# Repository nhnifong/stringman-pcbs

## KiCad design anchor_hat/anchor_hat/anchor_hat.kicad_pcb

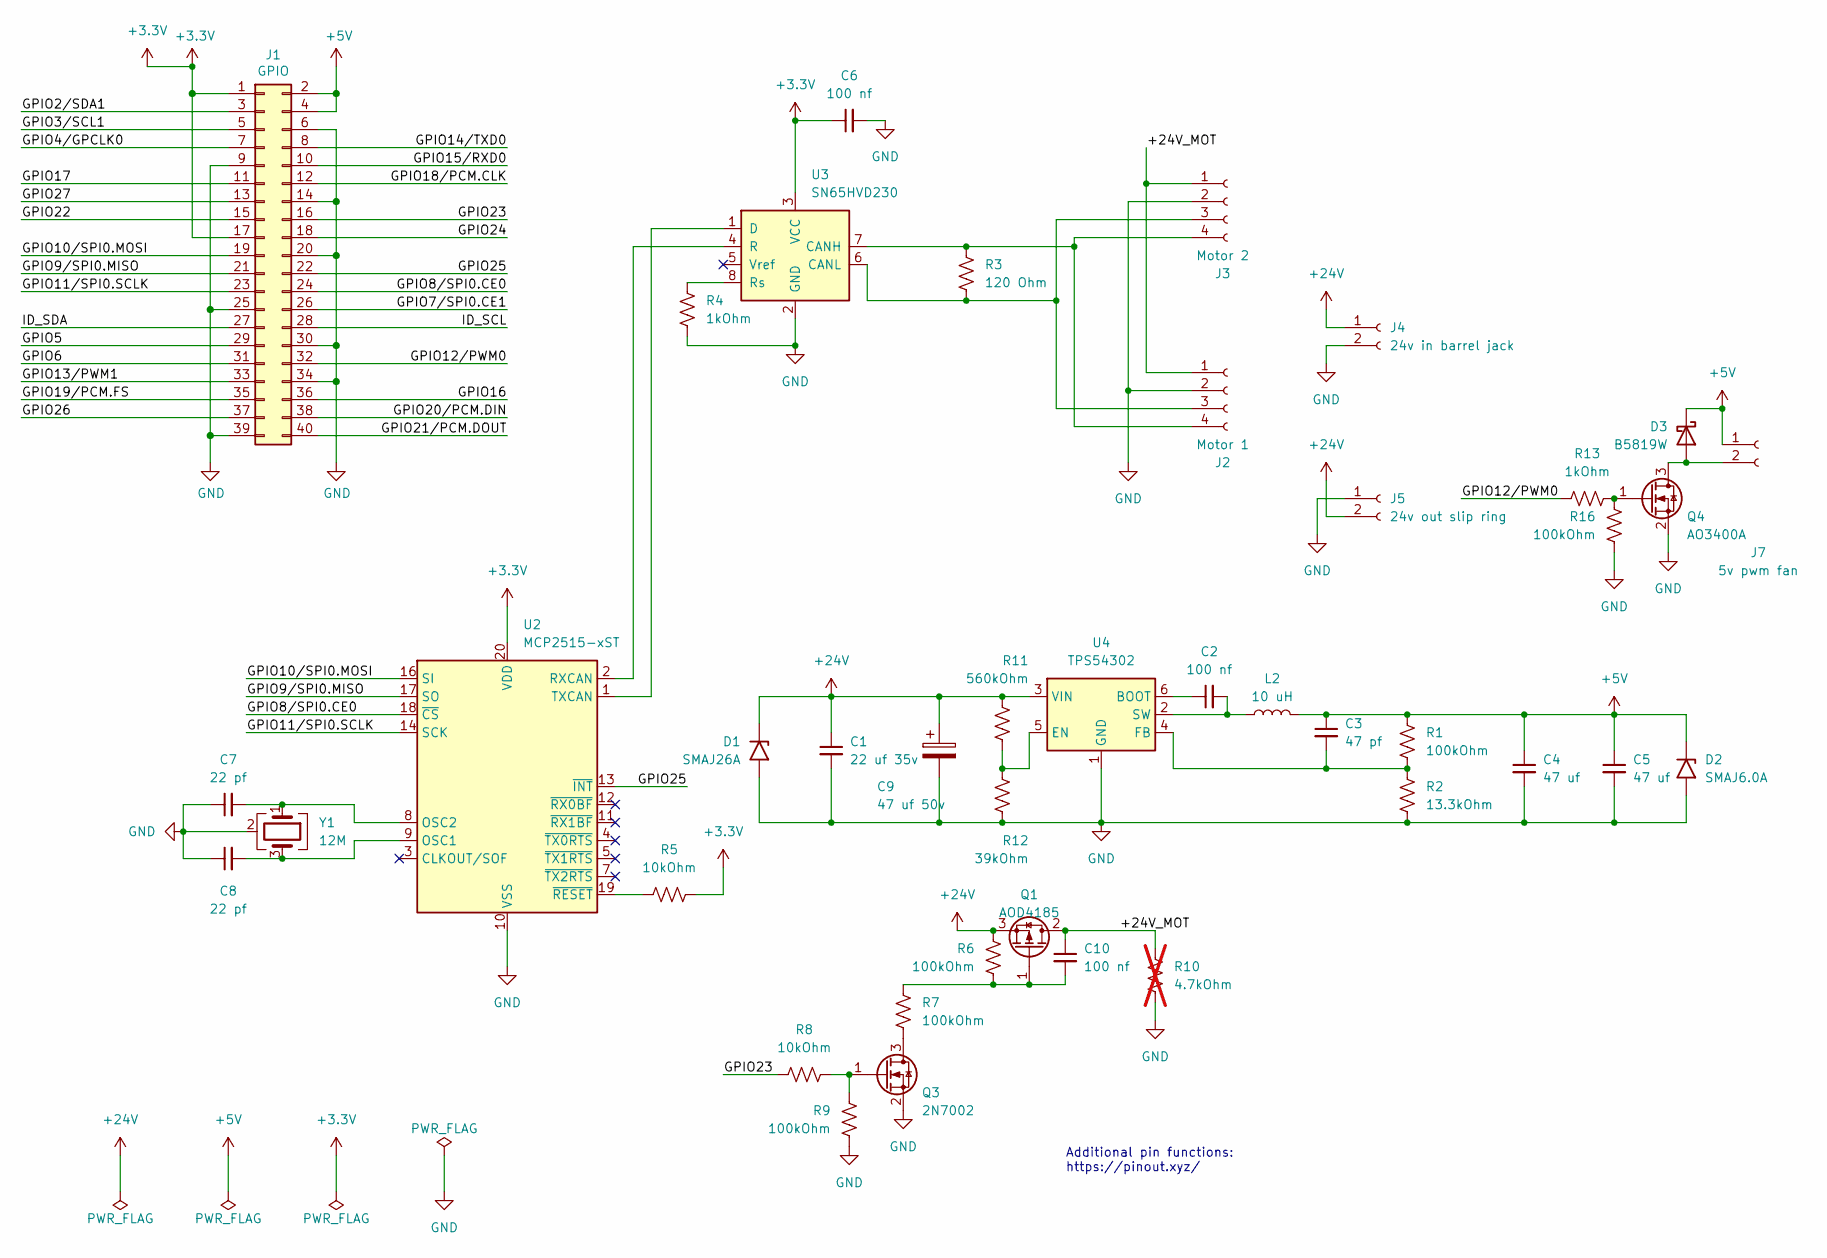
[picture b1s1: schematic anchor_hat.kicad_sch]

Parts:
C1: 22 uf 35v; C_1206_3216Metric
C2, C6, C10: 100 nf; C_0603_1608Metric
C3: 47 pf; C_0603_1608Metric
C4, C5: 47 uf; C_1206_3216Metric
C7, C8: 22 pf; C_0603_1608Metric
C9: 47 uf 50v; CP_Elec_6.3x7.7; jlc part C970679
D1: SMAJ26A; D_SMA; manufacturer part number SMAJ26A; jlc part C49370
D2: SMAJ6.0A; D_SMA; manufacturer part number SMAJ6.0A; jlc part C364284
D3: B5819W; D_SOD-123; manufacturer part number B5819W; jlc part C8598
J1: GPIO; PinSocket_2x20_P2.54mm_Vertical
J2: Motor 1; CONN-TH_4P-XT30PW-M; manufacturer part number XT30PW(2+2)-M.G.B; jlc part C19268030
J3: Motor 2; CONN-TH_4P-XT30PW-M; manufacturer part number XT30PW(2+2)-M.G.B; jlc part C19268030
J4: 24v in barrel jack; BarrelJack_vertical
J5: 24v out slip ring; JST_ZH_B2B-ZR-SM4-TF_1x02-1MP_P1.50mm_Vertical; jlc part C265284
J7: 5v pwm fan; JST_PH_B2B-PH-K_1x02_P2.00mm_Vertical
L2: 10 uH; IND-SMD_L8.0-W8.0_FNR80XXS; manufacturer part number FNR8040S100MT; jlc part C168127
Q1: AOD4185; TO-252-2; manufacturer part number AOD4185; jlc part C400894
Q3: 2N7002; SOT-23; manufacturer part number 2N7002; jlc part C8545
Q4: AO3400A; SOT-23; manufacturer part number AO3400A; jlc part C20917
R1, R6, R7, R9, R16: 100kOhm; R_0603_1608Metric
R2: 13.3kOhm; R_0603_1608Metric
R3: 120 Ohm; R_0603_1608Metric
R4, R13: 1kOhm; R_0603_1608Metric
R5, R8: 10kOhm; R_0603_1608Metric
R10: 4.7kOhm; R_1206_3216Metric; not fitted
R11: 560kOhm; R_0603_1608Metric
R12: 39kOhm; R_0603_1608Metric
U2: MCP2515-xST; TSSOP-20_4.4x6.5mm_P0.65mm; manufacturer part number MCP2515-I/ST; jlc part C15193
U3: SN65HVD230; SOIC-8_3.9x4.9mm_P1.27mm; manufacturer part number SN65HVD230DR; jlc part C12084
U4: TPS54302; SOT-23-6; manufacturer part number TPS54302DDCT; jlc part C311983
Y1: 12M; Crystal_SMD_3225-4Pin_3.2x2.5mm; manufacturer part number X322512MSB4SI; jlc part C9002

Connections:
+3.3V: C6.1, J1.1, J1.17, R5.2, U2.20 (VDD), U3.3 (VCC)
+5V: C3.1, C4.1, C5.1, D2.1 (A1), D3.1 (K), J1.2, J1.4, J7.1, L2.2, R1.1
+24V: C1.1, C9.1, D1.1 (A1), J4.1, J5.2, Q1.3 (S), R6.1, R11.1, U4.3 (VIN)
/+24V_MOT: C10.1, J2.1, J3.1, Q1.2 (D), R10.1
/GPIO2/SDA1: J1.3
/GPIO3/SCL1: J1.5
/GPIO4/GPCLK0: J1.7
/GPIO5: J1.29
/GPIO6: J1.31
/GPIO7/SPI0.CE1: J1.26
/GPIO8/SPI0.CE0: J1.24, U2.18 (~CS)
/GPIO9/SPI0.MISO: J1.21, U2.17 (SO)
/GPIO10/SPI0.MOSI: J1.19, U2.16 (SI)
/GPIO11/SPI0.SCLK: J1.23, U2.14 (SCK)
/GPIO12/PWM0: J1.32, R13.1
/GPIO13/PWM1: J1.33
/GPIO14/TXD0: J1.8
/GPIO15/RXD0: J1.10
/GPIO16: J1.36
/GPIO17: J1.11
/GPIO18/PCM.CLK: J1.12
/GPIO19/PCM.FS: J1.35
/GPIO20/PCM.DIN: J1.38
/GPIO21/PCM.DOUT: J1.40
/GPIO22: J1.15
/GPIO23: J1.16, R8.1
/GPIO24: J1.18
/GPIO25: J1.22, U2.13 (~INT)
/GPIO26: J1.37
/GPIO27: J1.13
/ID_SCL: J1.28
/ID_SDA: J1.27
GND: C1.2, C4.2, C5.2, C6.2, C7.1, C8.1, C9.2, D1.2 (A2), D2.2 (A2), J1.6, J1.9, J1.14, J1.20, J1.25, J1.30, J1.34, J1.39, J2.2, J3.2, J4.2, J5.1, Q3.2 (S), Q4.2 (S), R2.2, R4.2, R9.2, R10.2, R12.2, R16.2, U2.10 (VSS), U3.2 (GND), U4.1 (GND), Y1.2 (G), Y1.4 (G)
unnamed: D3.2 (A), J7.2, Q4.3 (D)
unnamed: J2.3, J3.3, R3.2, U3.6 (CANL)
unnamed: J2.4, J3.4, R3.1, U3.7 (CANH)
unnamed: C10.2, Q1.1 (G), R6.2, R7.1
unnamed: Q3.3 (D), R7.2
unnamed: Q3.1 (G), R8.2, R9.1
unnamed: Q4.1 (G), R13.2, R16.1
unnamed: C8.2, U2.9 (OSC1), Y1.3
unnamed: C7.2, U2.8 (OSC2), Y1.1
unnamed: U2.2 (RXCAN), U3.4 (R)
unnamed: U2.1 (TXCAN), U3.1 (D)
unnamed: R5.1, U2.19 (~RESET)
unnamed: R4.1, U3.8 (Rs)
unnamed: C2.1, U4.6 (BOOT)
unnamed: R11.2, R12.1, U4.5 (EN)
unnamed: C3.2, R1.2, R2.1, U4.4 (FB)
unnamed: C2.2, L2.1, U4.2 (SW)

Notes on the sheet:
Additional pin functions: https://pinout.xyz/

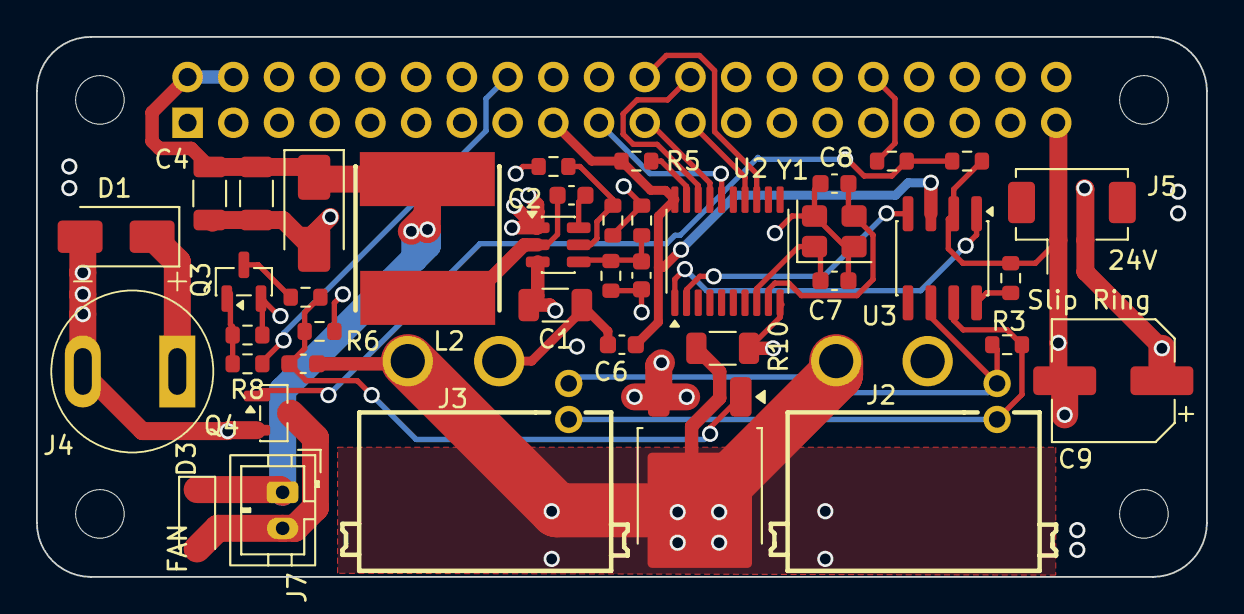
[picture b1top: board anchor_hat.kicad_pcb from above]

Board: 4 copper layers, 65.0 x 30.0 mm, 45 parts (1 on the bottom side), 29 nets.

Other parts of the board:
MH1, MH2, MH3, MH4: MountingHole_2.7mm_M2.5

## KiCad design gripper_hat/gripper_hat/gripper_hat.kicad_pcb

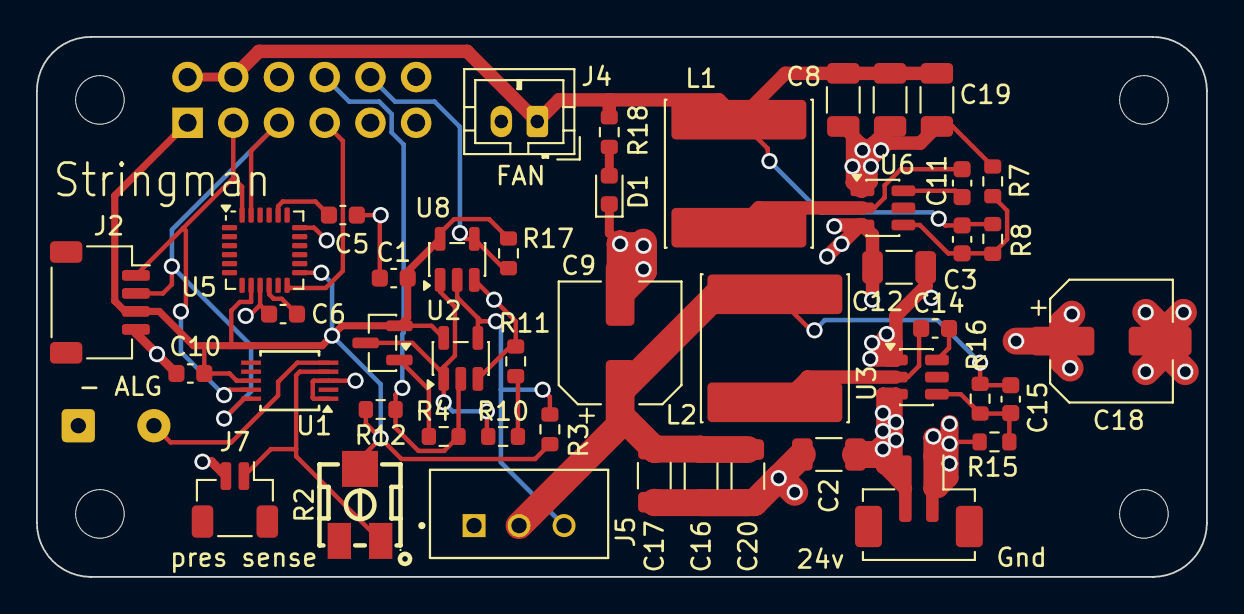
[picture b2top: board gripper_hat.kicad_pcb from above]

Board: 4 copper layers, 65.0 x 30.0 mm, 51 parts (1 on the bottom side), 25 nets.

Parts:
C1, C3, C6, C10, C14: 100nf; C_0603_1608Metric
C2, C12: 10 uf; C_1206_3216Metric
C4, C8, C16, C17, C19, C20: 22 uf; C_1206_3216Metric
C5: 22nf; C_0603_1608Metric
C9, C18: 100µF; CP_Elec_6.3x7.7
C11: 47 pf; C_0603_1608Metric
C15: 100 pf; C_0603_1608Metric
D1: LED; LED_0603_1608Metric
J1: GPIO; PinSocket_2x20_P2.54mm_Vertical
J2: SM04B-SRSS-TB(LF)(SN); JST_SH_SM04B-SRSS-TB_1x04-1MP_P1.00mm_Horizontal
J3: B2B-ZR-SM4-TF(LF)(SN); JST_ZH_B2B-ZR-SM4-TF_1x02-1MP_P1.50mm_Vertical
J4: 5v for fan; JST_PH_B2B-PH-K_1x02_P2.00mm_Vertical
J5: 22035035; MOLEX_22-03-5035
J6: extra analog breakout; SolderWire-0.25sqmm_1x02_P4.2mm_D0.65mm_OD1.7mm
J7: pres 1; JST_SH_BM02B-SRSS-TB_1x02-1MP_P1.00mm_Vertical
L1, L2: 12 uh; L_Sunlord_SWPA8040S
MH1, MH2, MH3, MH4: MountingHole_2.7mm_M2.5
Q1: SS8550; SOT-23
R2: R_Variable; RES-ADJ-SMD_3P-L4.5-W4.5-P2.30-BL-FS
R3, R4, R10, R11, R12, R17: 10k; R_0603_1608Metric
R7: 13.3kOhm; R_0603_1608Metric
R8, R16: 100kOhm; R_0603_1608Metric
R15: 8.66kOhm; R_0603_1608Metric
R18: 5.1k; R_0603_1608Metric
U1: ADS1015IDGS; TSSOP-10_3x3mm_P0.5mm
U2: SN74LVC1G126DBVR; SOT-23-5
U3, U6: TPS54302; SOT-23-6
U5: MPU-6050; InvenSense_QFN-24_4x4mm_P0.5mm
U8: SN74LVC1G125DBVR; SOT-23-5

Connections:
+3V3: C1.2, C10.2, J1.1, J2.3, Q1.2 (E), R2.2, R3.2, R12.2, R17.2, U1.8 (VDD), U2.5 (VCC), U5.8 (VLOGIC), U5.13 (VDD), U8.5 (VCC)
+5V: C4.1, C8.1, C11.2, C19.1, J1.2, J1.4, J4.1, L1.2, R8.2, R18.1
+24V: C2.1, C12.1, C18.1, J3.2, U3.3 (VIN), U6.3 (VIN)
/GPIO2/SDA1: J1.3, J2.1, U1.9 (SDA), U5.24 (SDA)
/GPIO3/SCL1: J1.5, J2.2, U1.10 (SCL), U5.23 (SCL)
/GPIO4/GPCLK0: J1.7, U5.12 (INT)
/GPIO14/TXD0: J1.8, R4.2, R12.1, U2.2
/GPIO15/RXD0: J1.10, R17.1, U8.4
GND: C1.1, C2.2, C4.2, C5.2, C6.2, C8.2, C9.2, C10.1, C12.2, C16.2, C17.2, C18.2, C19.2, C20.2, D1.1 (K), J1.6, J1.9, J2.4, J3.1, J4.2, J5.1, J6.1, J7.2, R7.1, R11.2, R15.1, U1.1 (ADDR), U1.3 (GND), U2.3 (GND), U3.1 (GND), U5.9 (AD0), U5.18 (GND), U6.1 (GND), U8.3 (GND)
unnamed: D1.2 (A), R18.2
unnamed: C9.1, C15.2, C16.1, C17.1, C20.1, J5.2, L2.2, R16.2
unnamed: J5.3, R3.1, U2.4, U8.2
unnamed: J6.2, U1.5 (AIN1)
unnamed: J7.1, R2.1, U1.4 (AIN0)
unnamed: Q1.1 (B), R4.1
unnamed: Q1.3 (C), R10.2, U2.1, U8.1
unnamed: R10.1, R11.1
unnamed: C14.1, U3.6 (BOOT)
unnamed: C15.1, R15.2, R16.1, U3.4 (FB)
unnamed: C14.2, L2.1, U3.2 (SW)
unnamed: C5.1, U5.20 (CPOUT)
unnamed: C6.1, U5.10 (REGOUT)
unnamed: C3.1, U6.6 (BOOT)
unnamed: C11.1, R7.2, R8.1, U6.4 (FB)
unnamed: C3.2, L1.1, U6.2 (SW)

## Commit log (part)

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2026-04-11 actual gripper hat that is being used
2026-05-27 add pot to gripper hat pressure sense divider
2026-06-15 add pinheader for alt fan plug type
